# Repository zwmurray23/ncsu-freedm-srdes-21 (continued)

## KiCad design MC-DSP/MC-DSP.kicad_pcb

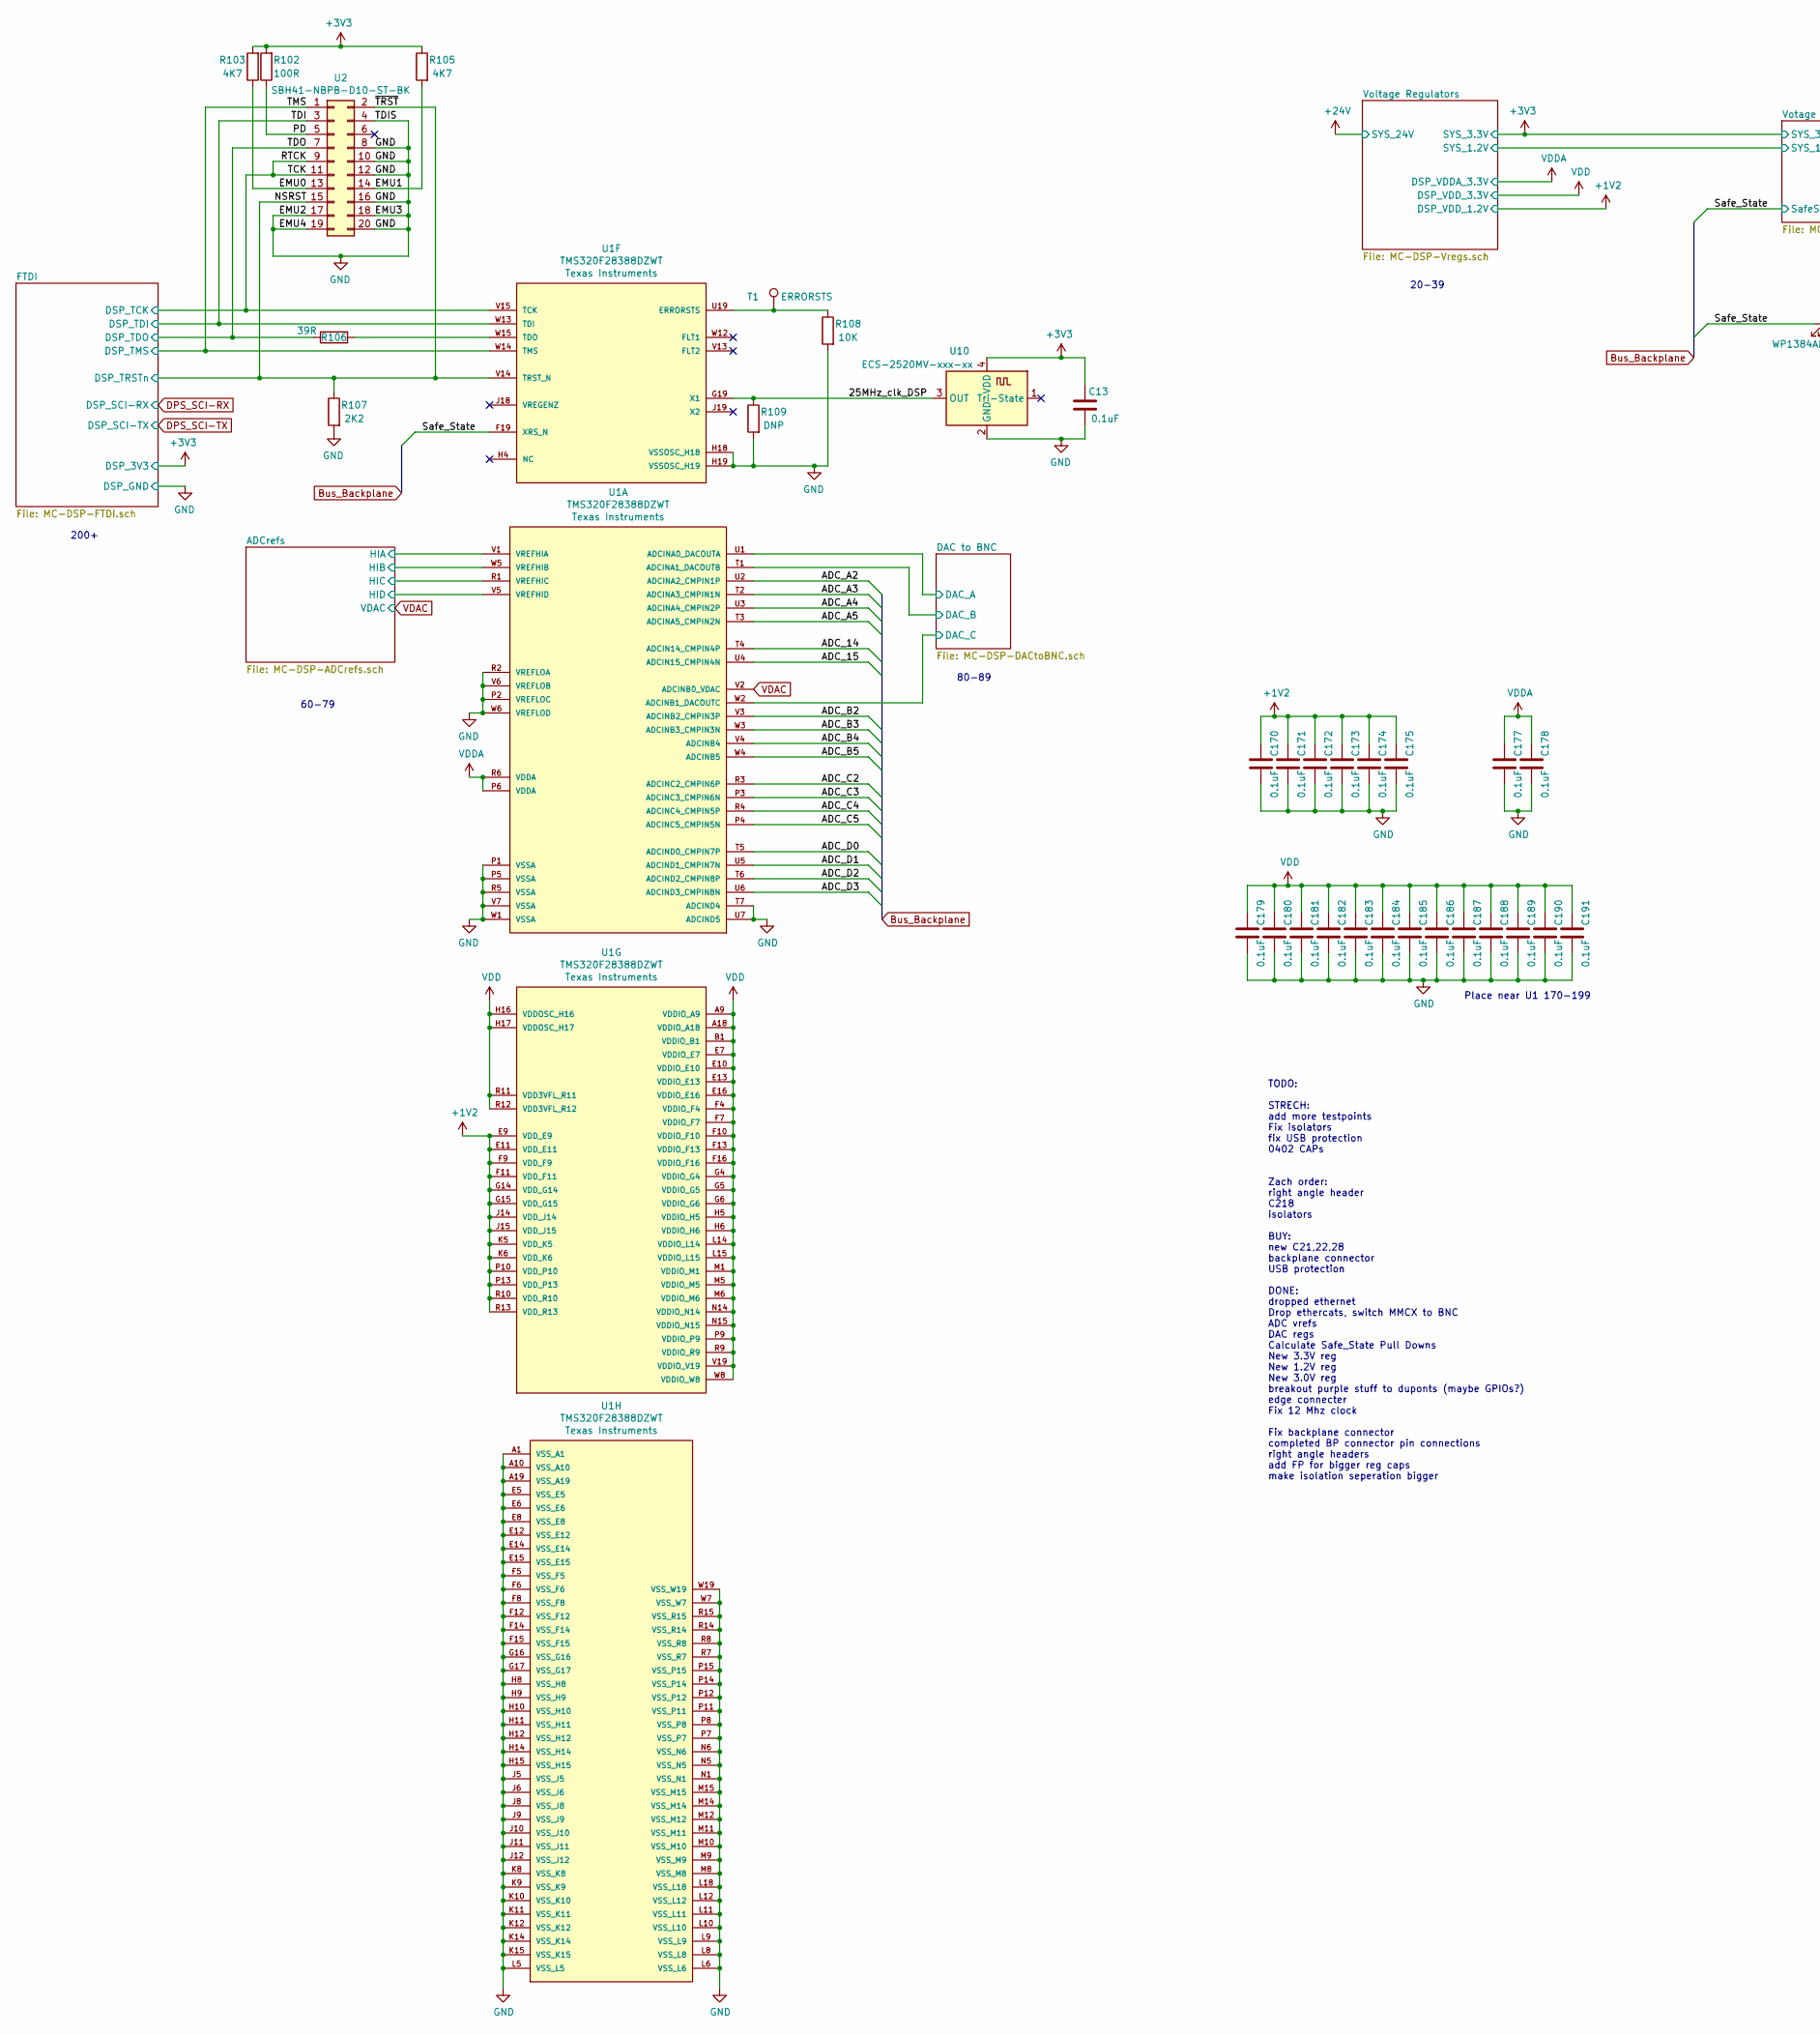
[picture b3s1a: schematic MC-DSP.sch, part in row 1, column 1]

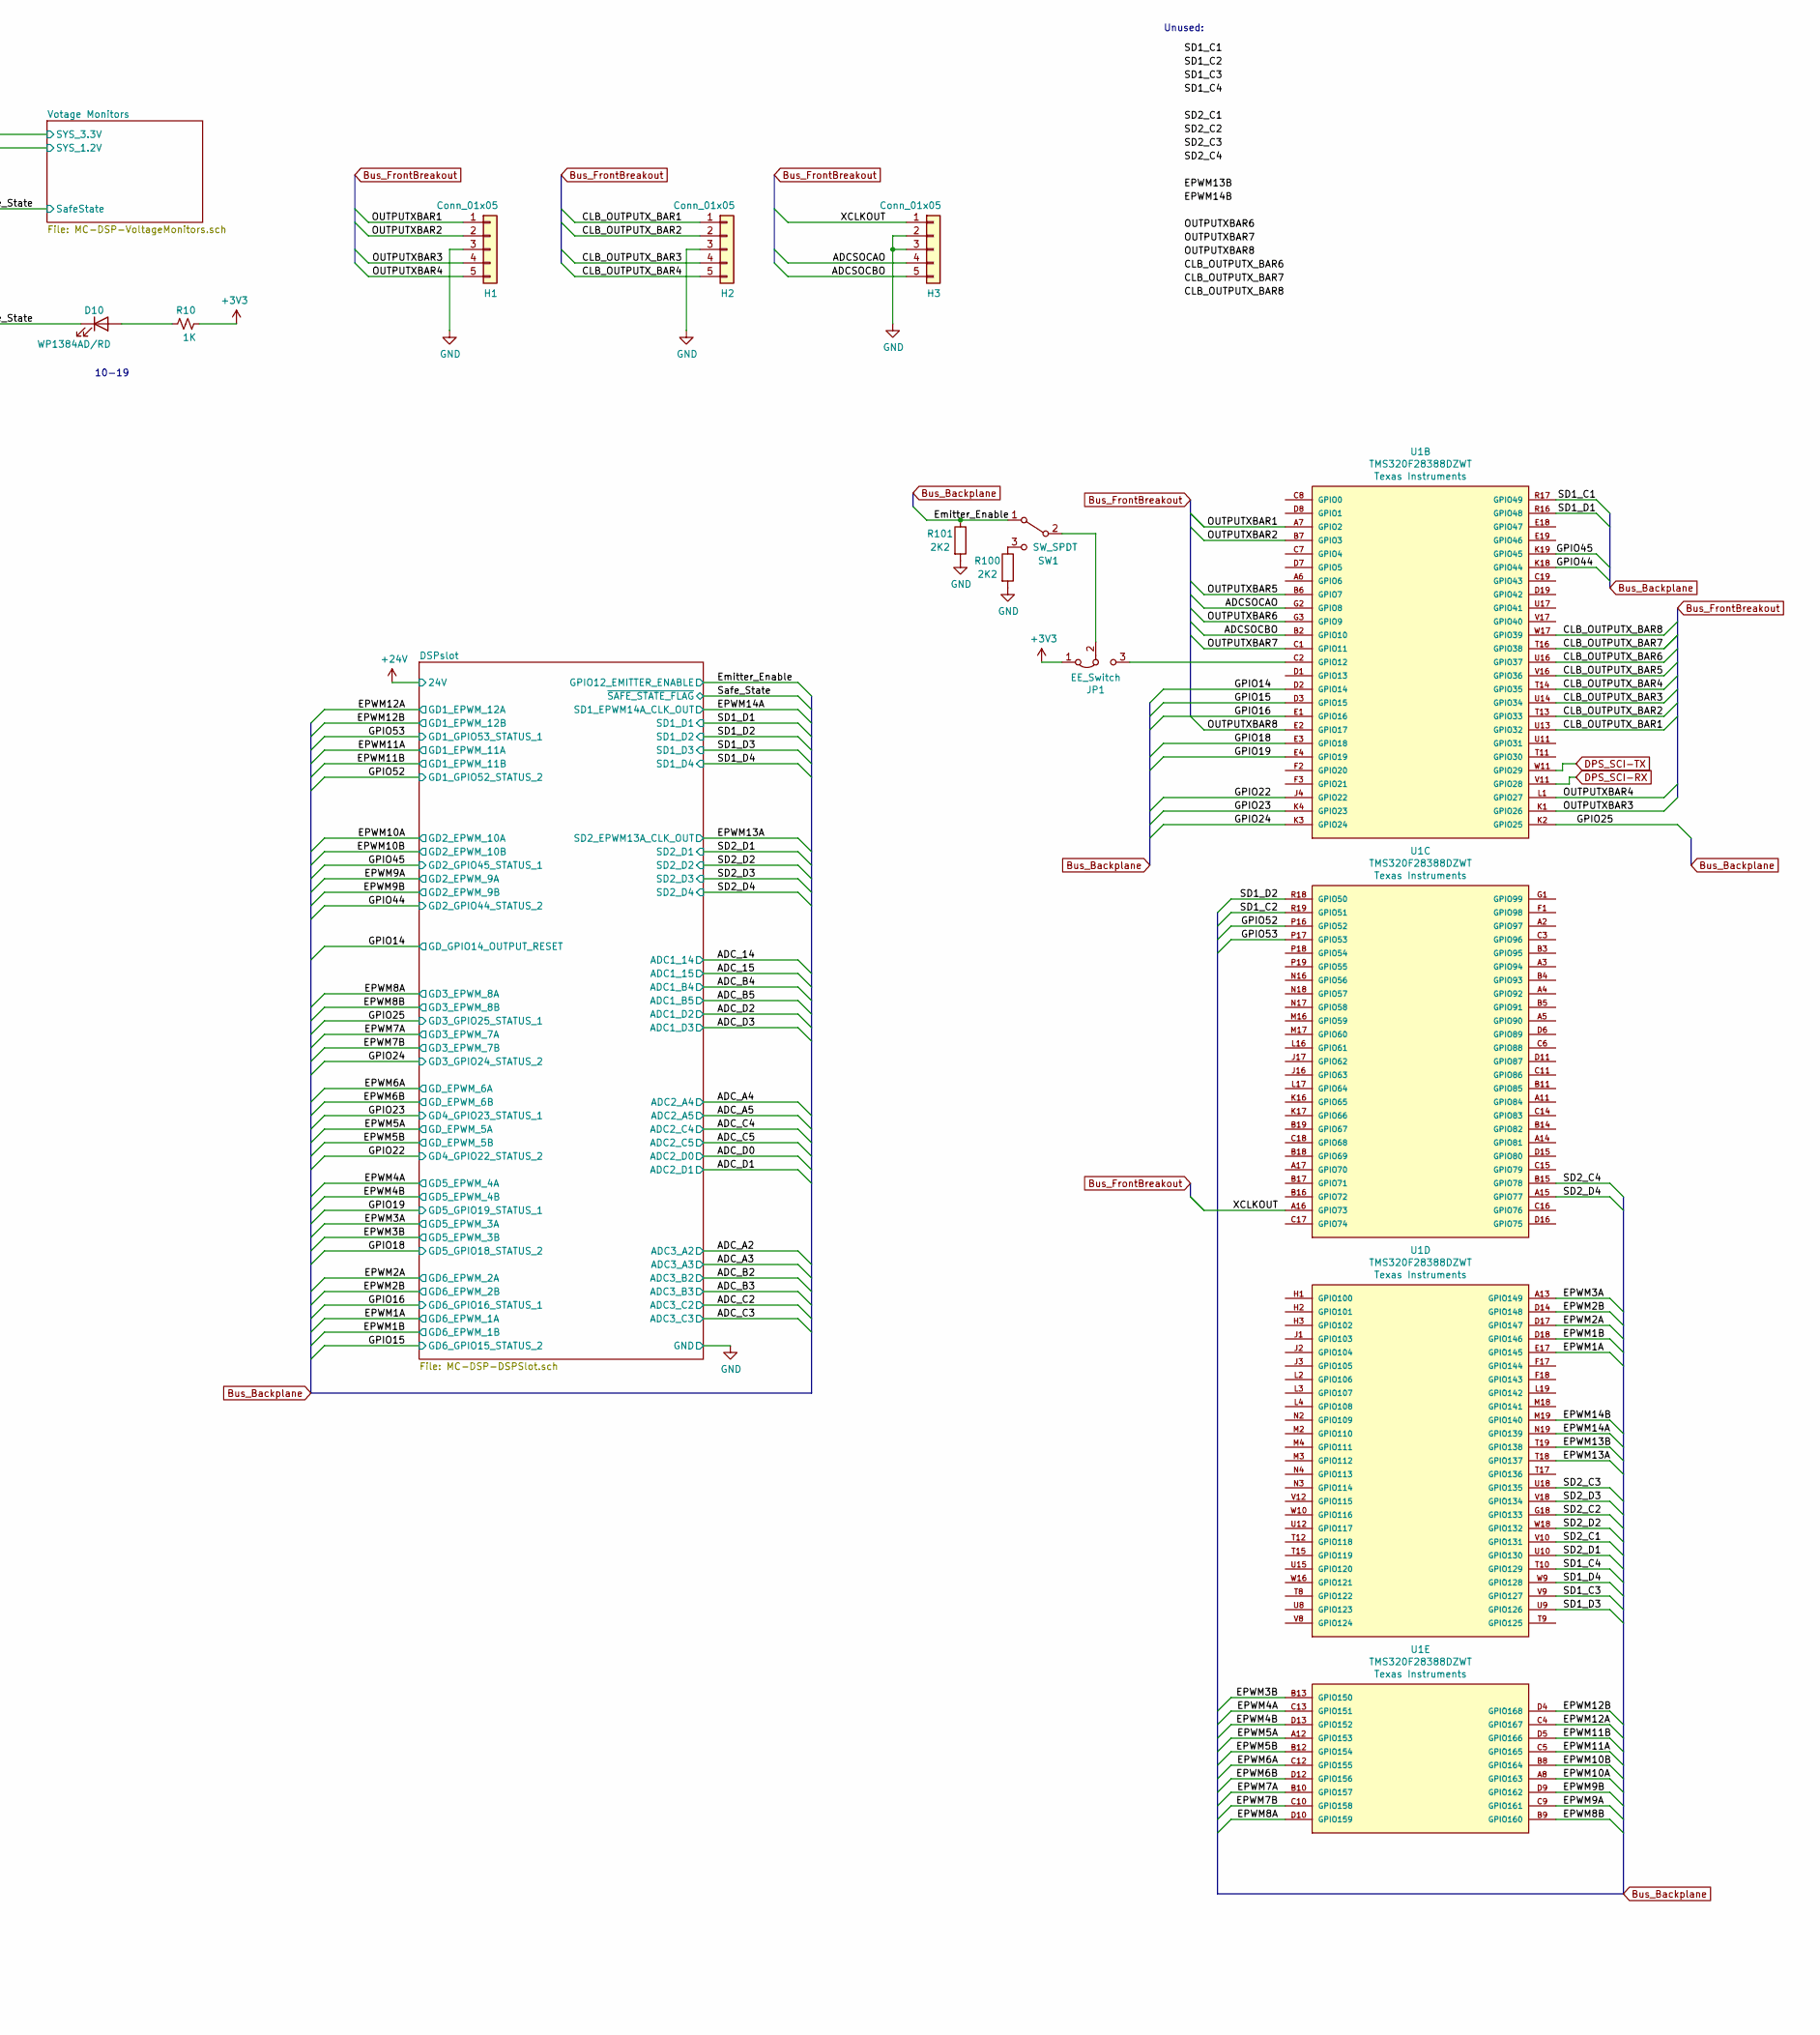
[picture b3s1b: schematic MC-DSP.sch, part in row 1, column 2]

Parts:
C13: 0.1uF; C_0603_1608Metric_Pad1.08x0.95mm_HandSolder
C170, C171, C172, C173, C174, C175, C177, C178, C179, C180, C181, C182, C183, C184, C185, C186, C187, C188, C189, C190, C191: 0.1uF; C_0402_1005Metric_Pad0.74x0.62mm_HandSolder
D10: WP1384AD/RD; LED_D3.0mm
H1, H2, H3: Conn_01x05; PinSocket_1x05_P2.54mm_Vertical
JP1: EE_Switch; PinSocket_1x03_P2.54mm_Vertical
R10: 1K; R_0603_1608Metric_Pad0.98x0.95mm_HandSolder
R100, R101, R107: 2K2; R_0603_1608Metric_Pad0.98x0.95mm_HandSolder
R102: 100R; R_0603_1608Metric_Pad0.98x0.95mm_HandSolder
R103, R105: 4K7; R_0603_1608Metric_Pad0.98x0.95mm_HandSolder
R106: 39R; R_0603_1608Metric_Pad0.98x0.95mm_HandSolder
R108: 10K; R_0603_1608Metric_Pad0.98x0.95mm_HandSolder
R109: DNP; R_0603_1608Metric_Pad0.98x0.95mm_HandSolder
SW1: SW_SPDT; GT12MABE
T1: ERRORSTS; TestPoint_Pad_D1.5mm
U1: TMS320F28388DZWT; BGA337C80P19X19_1600X1600X140N
U2: SBH41-NBPB-D10-ST-BK
U10: ECS-2520MV-xxx-xx; Oscillator_SMD_ECS_2520MV-xxx-xx-4Pin_2.5x2.0mm

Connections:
+1V2: C170.2, C171.2, C172.2, C173.2, C174.2, C175.2, U1.E9 (VDD_E9), U1.E11 (VDD_E11), U1.F9 (VDD_F9), U1.F11 (VDD_F11), U1.G14 (VDD_G14), U1.G15 (VDD_G15), U1.J14 (VDD_J14), U1.J15 (VDD_J15), U1.K5 (VDD_K5), U1.K6 (VDD_K6), U1.P10 (VDD_P10), U1.P13 (VDD_P13), U1.R10 (VDD_R10), U1.R13 (VDD_R13); also elsewhere on the board
+3V3: C13.2, JP1.1 (A), R10.1, R102.2, R103.2, R105.1, U10.4 (VDD); also elsewhere on the board
/25MHz_clk_DSP: R109.1, U1.G19 (X1), U10.3 (OUT)
/ADCSOCAO: H3.4, U1.G2 (GPIO8)
/ADCSOCBO: H3.5, U1.B2 (GPIO10)
/ADC_14: U1.T4 (ADCIN14_CMPIN4P); also elsewhere on the board
/ADC_15: U1.U4 (ADCIN15_CMPIN4N); also elsewhere on the board
/ADC_A2: U1.U2 (ADCINA2_CMPIN1P); also elsewhere on the board
/ADC_A3: U1.T2 (ADCINA3_CMPIN1N); also elsewhere on the board
/ADC_A4: U1.U3 (ADCINA4_CMPIN2P); also elsewhere on the board
/ADC_A5: U1.T3 (ADCINA5_CMPIN2N); also elsewhere on the board
/ADC_B2: U1.V3 (ADCINB2_CMPIN3P); also elsewhere on the board
/ADC_B3: U1.W3 (ADCINB3_CMPIN3N); also elsewhere on the board
/ADC_B4: U1.V4 (ADCINB4); also elsewhere on the board
/ADC_B5: U1.W4 (ADCINB5); also elsewhere on the board
/ADC_C2: U1.R3 (ADCINC2_CMPIN6P); also elsewhere on the board
/ADC_C3: U1.P3 (ADCINC3_CMPIN6N); also elsewhere on the board
/ADC_C4: U1.R4 (ADCINC4_CMPIN5P); also elsewhere on the board
/ADC_C5: U1.P4 (ADCINC5_CMPIN5N); also elsewhere on the board
/ADC_D0: U1.T5 (ADCIND0_CMPIN7P); also elsewhere on the board
/ADC_D1: U1.U5 (ADCIND1_CMPIN7N); also elsewhere on the board
/ADC_D2: U1.T6 (ADCIND2_CMPIN8P); also elsewhere on the board
/ADC_D3: U1.U6 (ADCIND3_CMPIN8N); also elsewhere on the board
/ADCrefs/HIA: U1.V1 (VREFHIA); also elsewhere on the board
/ADCrefs/HIB: U1.W5 (VREFHIB); also elsewhere on the board
/ADCrefs/HIC: U1.R1 (VREFHIC); also elsewhere on the board
/ADCrefs/HID: U1.V5 (VREFHID); also elsewhere on the board
/CLB_OUTPUTX_BAR1: H2.1, U1.U13 (GPIO32)
/CLB_OUTPUTX_BAR2: H2.2, U1.T13 (GPIO33)
/CLB_OUTPUTX_BAR3: H2.4, U1.U14 (GPIO34)
/CLB_OUTPUTX_BAR4: H2.5, U1.T14 (GPIO35)
/CLB_OUTPUTX_BAR5: U1.V16 (GPIO36)
/CLB_OUTPUTX_BAR6: U1.U16 (GPIO37)
/CLB_OUTPUTX_BAR7: U1.T16 (GPIO38)
/CLB_OUTPUTX_BAR8: U1.W17 (GPIO39)
/DAC to BNC/DAC_A: U1.U1 (ADCINA0_DACOUTA); also elsewhere on the board
/DAC to BNC/DAC_B: U1.T1 (ADCINA1_DACOUTB); also elsewhere on the board
/DAC to BNC/DAC_C: U1.W2 (ADCINB1_DACOUTC); also elsewhere on the board
/EMU0: R103.1, U2.13
/EMU1: R105.2, U2.14
/EPWM1A: U1.E17 (GPIO145); also elsewhere on the board
/EPWM1B: U1.D18 (GPIO146); also elsewhere on the board
/EPWM2A: U1.D17 (GPIO147); also elsewhere on the board
/EPWM2B: U1.D14 (GPIO148); also elsewhere on the board
/EPWM3A: U1.A13 (GPIO149); also elsewhere on the board
/EPWM3B: U1.B13 (GPIO150); also elsewhere on the board
/EPWM4A: U1.C13 (GPIO151); also elsewhere on the board
/EPWM4B: U1.D13 (GPIO152); also elsewhere on the board
/EPWM5A: U1.A12 (GPIO153); also elsewhere on the board
/EPWM5B: U1.B12 (GPIO154); also elsewhere on the board
/EPWM6A: U1.C12 (GPIO155); also elsewhere on the board
/EPWM6B: U1.D12 (GPIO156); also elsewhere on the board
/EPWM7A: U1.B10 (GPIO157); also elsewhere on the board
/EPWM7B: U1.C10 (GPIO158); also elsewhere on the board
/EPWM8A: U1.D10 (GPIO159); also elsewhere on the board
/EPWM8B: U1.B9 (GPIO160); also elsewhere on the board
/EPWM9A: U1.C9 (GPIO161); also elsewhere on the board
/EPWM9B: U1.D9 (GPIO162); also elsewhere on the board
/EPWM10A: U1.A8 (GPIO163); also elsewhere on the board
/EPWM10B: U1.B8 (GPIO164); also elsewhere on the board
/EPWM11A: U1.C5 (GPIO165); also elsewhere on the board
/EPWM11B: U1.D5 (GPIO166); also elsewhere on the board
/EPWM12A: U1.C4 (GPIO167); also elsewhere on the board
/EPWM12B: U1.D4 (GPIO168); also elsewhere on the board
/EPWM13A: U1.T18 (GPIO137); also elsewhere on the board
/EPWM13B: U1.T19 (GPIO138)
/EPWM14A: U1.N19 (GPIO139); also elsewhere on the board
/EPWM14B: U1.M19 (GPIO140)
/Emitter_Enable: R101.1, SW1.1 (A); also elsewhere on the board
/GPIO14: U1.D2 (GPIO14); also elsewhere on the board
/GPIO15: U1.D3 (GPIO15); also elsewhere on the board
/GPIO16: U1.E1 (GPIO16); also elsewhere on the board
/GPIO18: U1.E3 (GPIO18); also elsewhere on the board
/GPIO19: U1.E4 (GPIO19); also elsewhere on the board
/GPIO22: U1.J4 (GPIO22); also elsewhere on the board
/GPIO23: U1.K4 (GPIO23); also elsewhere on the board
/GPIO24: U1.K3 (GPIO24); also elsewhere on the board
/GPIO25: U1.K2 (GPIO25); also elsewhere on the board
/GPIO44: U1.K18 (GPIO44); also elsewhere on the board
/GPIO45: U1.K19 (GPIO45); also elsewhere on the board
/GPIO52: U1.P16 (GPIO52); also elsewhere on the board
/GPIO53: U1.P17 (GPIO53); also elsewhere on the board
/NSRST: R107.1, U1.V14 (TRST_N), U2.2, U2.15; also elsewhere on the board
/OUTPUTXBAR1: H1.1, U1.A7 (GPIO2)
/OUTPUTXBAR2: H1.2, U1.B7 (GPIO3)
/OUTPUTXBAR3: H1.4, U1.K1 (GPIO26)
/OUTPUTXBAR4: H1.5, U1.L1 (GPIO27)
/OUTPUTXBAR5: U1.B6 (GPIO7)
/OUTPUTXBAR6: U1.G3 (GPIO9)
/OUTPUTXBAR7: U1.C1 (GPIO11)
/OUTPUTXBAR8: U1.E2 (GPIO17)
/PD: R102.1, U2.5
/RTCK: U1.V15 (TCK), U2.9, U2.11; also elsewhere on the board
/SD1_C1: U1.R17 (GPIO49)
/SD1_C2: U1.R19 (GPIO51)
/SD1_C3: U1.V9 (GPIO127)
/SD1_C4: U1.T10 (GPIO129)
/SD1_D1: U1.R16 (GPIO48); also elsewhere on the board
/SD1_D2: U1.R18 (GPIO50); also elsewhere on the board
/SD1_D3: U1.U9 (GPIO126); also elsewhere on the board
/SD1_D4: U1.W9 (GPIO128); also elsewhere on the board
/SD2_C1: U1.V10 (GPIO131)
/SD2_C2: U1.G18 (GPIO133)
/SD2_C3: U1.U18 (GPIO135)
/SD2_C4: U1.B15 (GPIO78)
/SD2_D1: U1.U10 (GPIO130); also elsewhere on the board
/SD2_D2: U1.W18 (GPIO132); also elsewhere on the board
/SD2_D3: U1.V18 (GPIO134); also elsewhere on the board
/SD2_D4: U1.A15 (GPIO77); also elsewhere on the board
/Safe_State: D10.1 (K), U1.F19 (XRS_N); also elsewhere on the board
/TDI: U1.W13 (TDI), U2.3; also elsewhere on the board
/TDO: R106.1, U2.7; also elsewhere on the board
/TMS: U1.W14 (TMS), U2.1; also elsewhere on the board
/XCLKOUT: H3.1, U1.A16 (GPIO73)
DPS_SCI-RX: U1.V11 (GPIO28); also elsewhere on the board
DPS_SCI-TX: U1.W11 (GPIO29); also elsewhere on the board
GND: C13.1, C170.1, C171.1, C172.1, C173.1, C174.1, C175.1, C177.1, C178.1, C179.1, C180.1, C181.1, C182.1, C183.1, C184.1, C185.1, C186.1, C187.1, C188.1, C189.1, C190.1, C191.1, H1.3, H2.3, H3.2, H3.3, R100.2, R101.2, R107.2, R108.2, R109.2, U1.A1 (VSS_A1), U1.A10 (VSS_A10), U1.A19 (VSS_A19), U1.E5 (VSS_E5), U1.E6 (VSS_E6), U1.E8 (VSS_E8), U1.E12 (VSS_E12), U1.E14 (VSS_E14), U1.E15 (VSS_E15), U1.F5 (VSS_F5), U1.F6 (VSS_F6), U1.F8 (VSS_F8), U1.F12 (VSS_F12), U1.F14 (VSS_F14), U1.F15 (VSS_F15), U1.G16 (VSS_G16), U1.G17 (VSS_G17), U1.H8 (VSS_H8), U1.H9 (VSS_H9), U1.H10 (VSS_H10), U1.H11 (VSS_H11), U1.H12 (VSS_H12), U1.H14 (VSS_H14), U1.H15 (VSS_H15), U1.H18 (VSSOSC_H18), U1.H19 (VSSOSC_H19), U1.J5 (VSS_J5), U1.J6 (VSS_J6), U1.J8 (VSS_J8), U1.J9 (VSS_J9), U1.J10 (VSS_J10), U1.J11 (VSS_J11), U1.J12 (VSS_J12), U1.K8 (VSS_K8), U1.K9 (VSS_K9), U1.K10 (VSS_K10), U1.K11 (VSS_K11), U1.K12 (VSS_K12), U1.K14 (VSS_K14), U1.K15 (VSS_K15), U1.L5 (VSS_L5), U1.L6 (VSS_L6), U1.L8 (VSS_L8), U1.L9 (VSS_L9), U1.L10 (VSS_L10), U1.L11 (VSS_L11), U1.L12 (VSS_L12), U1.L18 (VSS_L18), U1.M8 (VSS_M8), U1.M9 (VSS_M9), U1.M10 (VSS_M10), U1.M11 (VSS_M11), U1.M12 (VSS_M12), U1.M14 (VSS_M14), U1.M15 (VSS_M15), U1.N1 (VSS_N1), U1.N5 (VSS_N5), U1.N6 (VSS_N6), U1.P1 (VSSA), U1.P2 (VREFLOC), U1.P5 (VSSA), U1.P7 (VSS_P7), U1.P8 (VSS_P8), U1.P11 (VSS_P11), U1.P12 (VSS_P12), U1.P14 (VSS_P14), U1.P15 (VSS_P15), U1.R2 (VREFLOA), U1.R5 (VSSA), U1.R7 (VSS_R7), U1.R8 (VSS_R8), U1.R14 (VSS_R14), U1.R15 (VSS_R15), U1.T7 (ADCIND4), U1.U7 (ADCIND5), U1.V6 (VREFLOB), U1.V7 (VSSA), U1.W1 (VSSA), U1.W6 (VREFLOD), U1.W7 (VSS_W7), U1.W19 (VSS_W19), U2.4, U2.8, U2.10, U2.12, U2.16, U2.17, U2.18, U2.19, U2.20, U10.2 (GND); also elsewhere on the board
unnamed: D10.2 (A), R10.2
unnamed: JP1.2 (C), SW1.2 (B)
unnamed: JP1.3 (B), U1.C2 (GPIO12)
unnamed: R100.1, SW1.3 (C)
unnamed: R106.2, U1.W15 (TDO)
unnamed: R108.1, T1.1, U1.U19 (ERRORSTS)
VDAC: U1.V2 (ADCINB0_VDAC); also elsewhere on the board
VDD: C179.2, C180.2, C181.2, C182.2, C183.2, C184.2, C185.2, C186.2, C187.2, C188.2, C189.2, C190.2, C191.2, U1.A9 (VDDIO_A9), U1.A18 (VDDIO_A18), U1.B1 (VDDIO_B1), U1.E7 (VDDIO_E7), U1.E10 (VDDIO_E10), U1.E13 (VDDIO_E13), U1.E16 (VDDIO_E16), U1.F4 (VDDIO_F4), U1.F7 (VDDIO_F7), U1.F10 (VDDIO_F10), U1.F13 (VDDIO_F13), U1.F16 (VDDIO_F16), U1.G4 (VDDIO_G4), U1.G5 (VDDIO_G5), U1.G6 (VDDIO_G6), U1.H5 (VDDIO_H5), U1.H6 (VDDIO_H6), U1.H16 (VDDOSC_H16), U1.H17 (VDDOSC_H17), U1.L14 (VDDIO_L14), U1.L15 (VDDIO_L15), U1.M1 (VDDIO_M1), U1.M5 (VDDIO_M5), U1.M6 (VDDIO_M6), U1.N14 (VDDIO_N14), U1.N15 (VDDIO_N15), U1.P9 (VDDIO_P9), U1.R9 (VDDIO_R9), U1.R11 (VDD3VFL_R11), U1.R12 (VDD3VFL_R12), U1.V19 (VDDIO_V19), U1.W8 (VDDIO_W8); also elsewhere on the board
VDDA: C177.2, C178.2, U1.P6 (VDDA), U1.R6 (VDDA); also elsewhere on the board

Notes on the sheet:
60-79
80-89
200+
10-19
20-39
Place near U1 170-199
TODO: STRECH: add more testpoints Fix isolators fix USB protection 0402 CAPs Zach order: right angle header C218 isolators BUY: new C21,22,28 backplane connector USB protection DONE: dropped ethernet Drop ethercats, switch MMCX to BNC ADC vrefs DAC regs Calculate Safe_State Pull Downs New 3.3V reg 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
Unused:

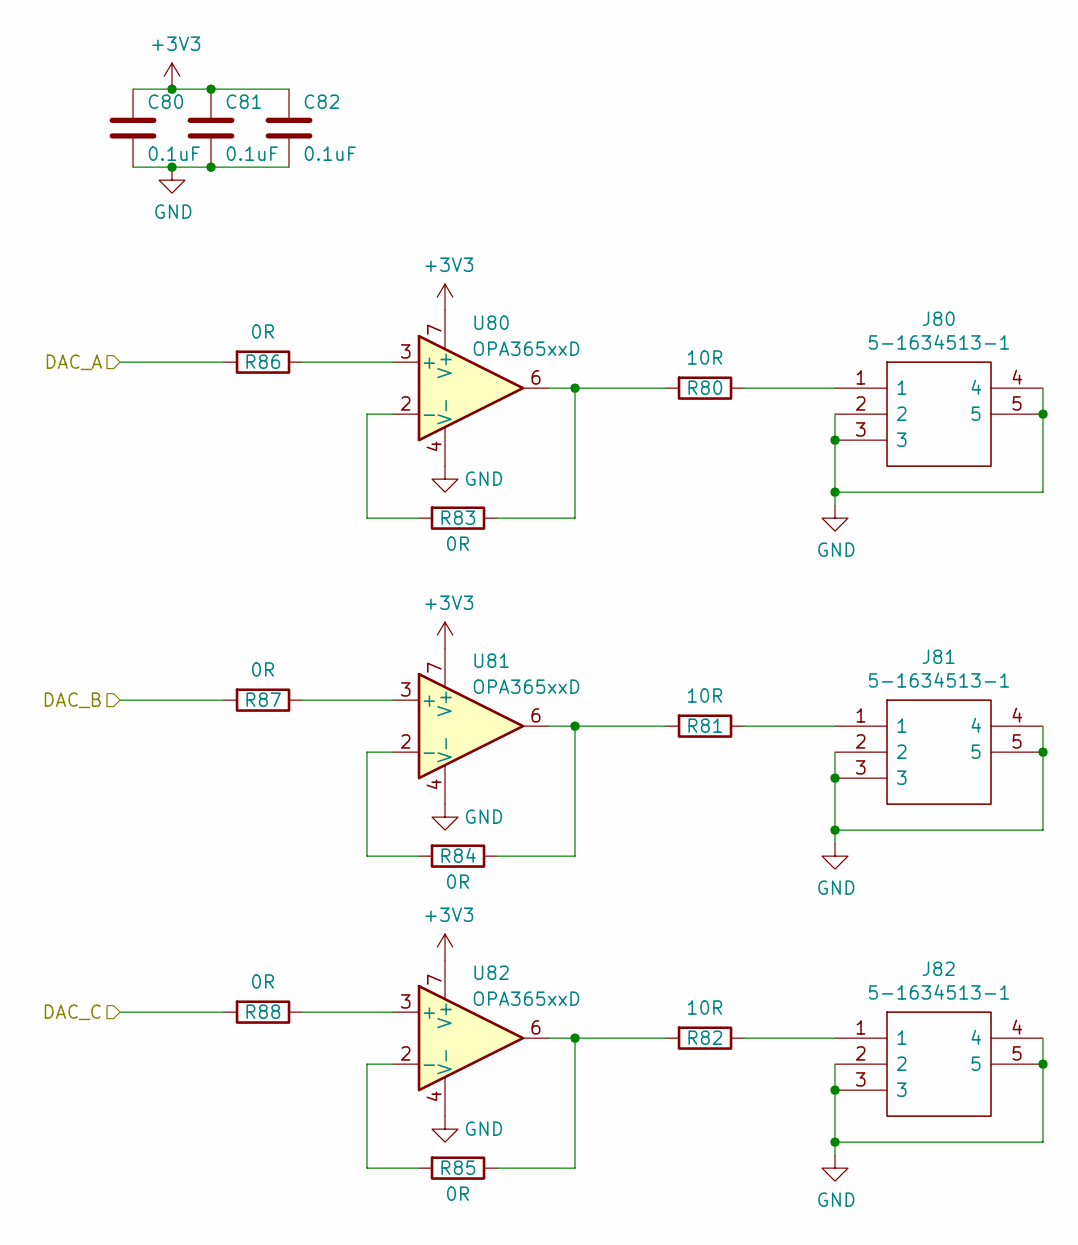
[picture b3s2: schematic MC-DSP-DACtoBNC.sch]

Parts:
C80, C81, C82: 0.1uF; C_0603_1608Metric_Pad1.08x0.95mm_HandSolder
J80, J81, J82: 5-1634513-1; 516345131; Manufacturer_Part_Number 5-1634513-1; Mouser Part Number 571-5-1634513-1
R80, R81, R82: 10R; R_0603_1608Metric_Pad0.98x0.95mm_HandSolder
R83, R84, R85, R86, R87, R88: 0R; R_0603_1608Metric_Pad0.98x0.95mm_HandSolder
U80, U81, U82: OPA365xxD; SOIC-8_3.9x4.9mm_P1.27mm

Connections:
+3V3: C80.2, C81.2, C82.2, U80.7 (V+), U81.7 (V+), U82.7 (V+); also elsewhere on the board
/DAC to BNC/DAC_A: R86.2; also elsewhere on the board
/DAC to BNC/DAC_B: R87.2; also elsewhere on the board
/DAC to BNC/DAC_C: R88.2; also elsewhere on the board
GND: C80.1, C81.1, C82.1, J80.2, J80.3, J80.4, J80.5, J81.2, J81.3, J81.4, J81.5, J82.2, J82.3, J82.4, J82.5, U80.4 (V-), U81.4 (V-), U82.4 (V-); also elsewhere on the board
unnamed: J80.1, R80.1
unnamed: J81.1, R81.1
unnamed: J82.1, R82.1
unnamed: R80.2, R83.1, U80.6
unnamed: R81.2, R84.1, U81.6
unnamed: R82.2, R85.1, U82.6
unnamed: R83.2, U80.2 (-)
unnamed: R84.2, U81.2 (-)
unnamed: R85.2, U82.2 (-)
unnamed: R86.1, U80.3 (+)
unnamed: R87.1, U81.3 (+)
unnamed: R88.1, U82.3 (+)

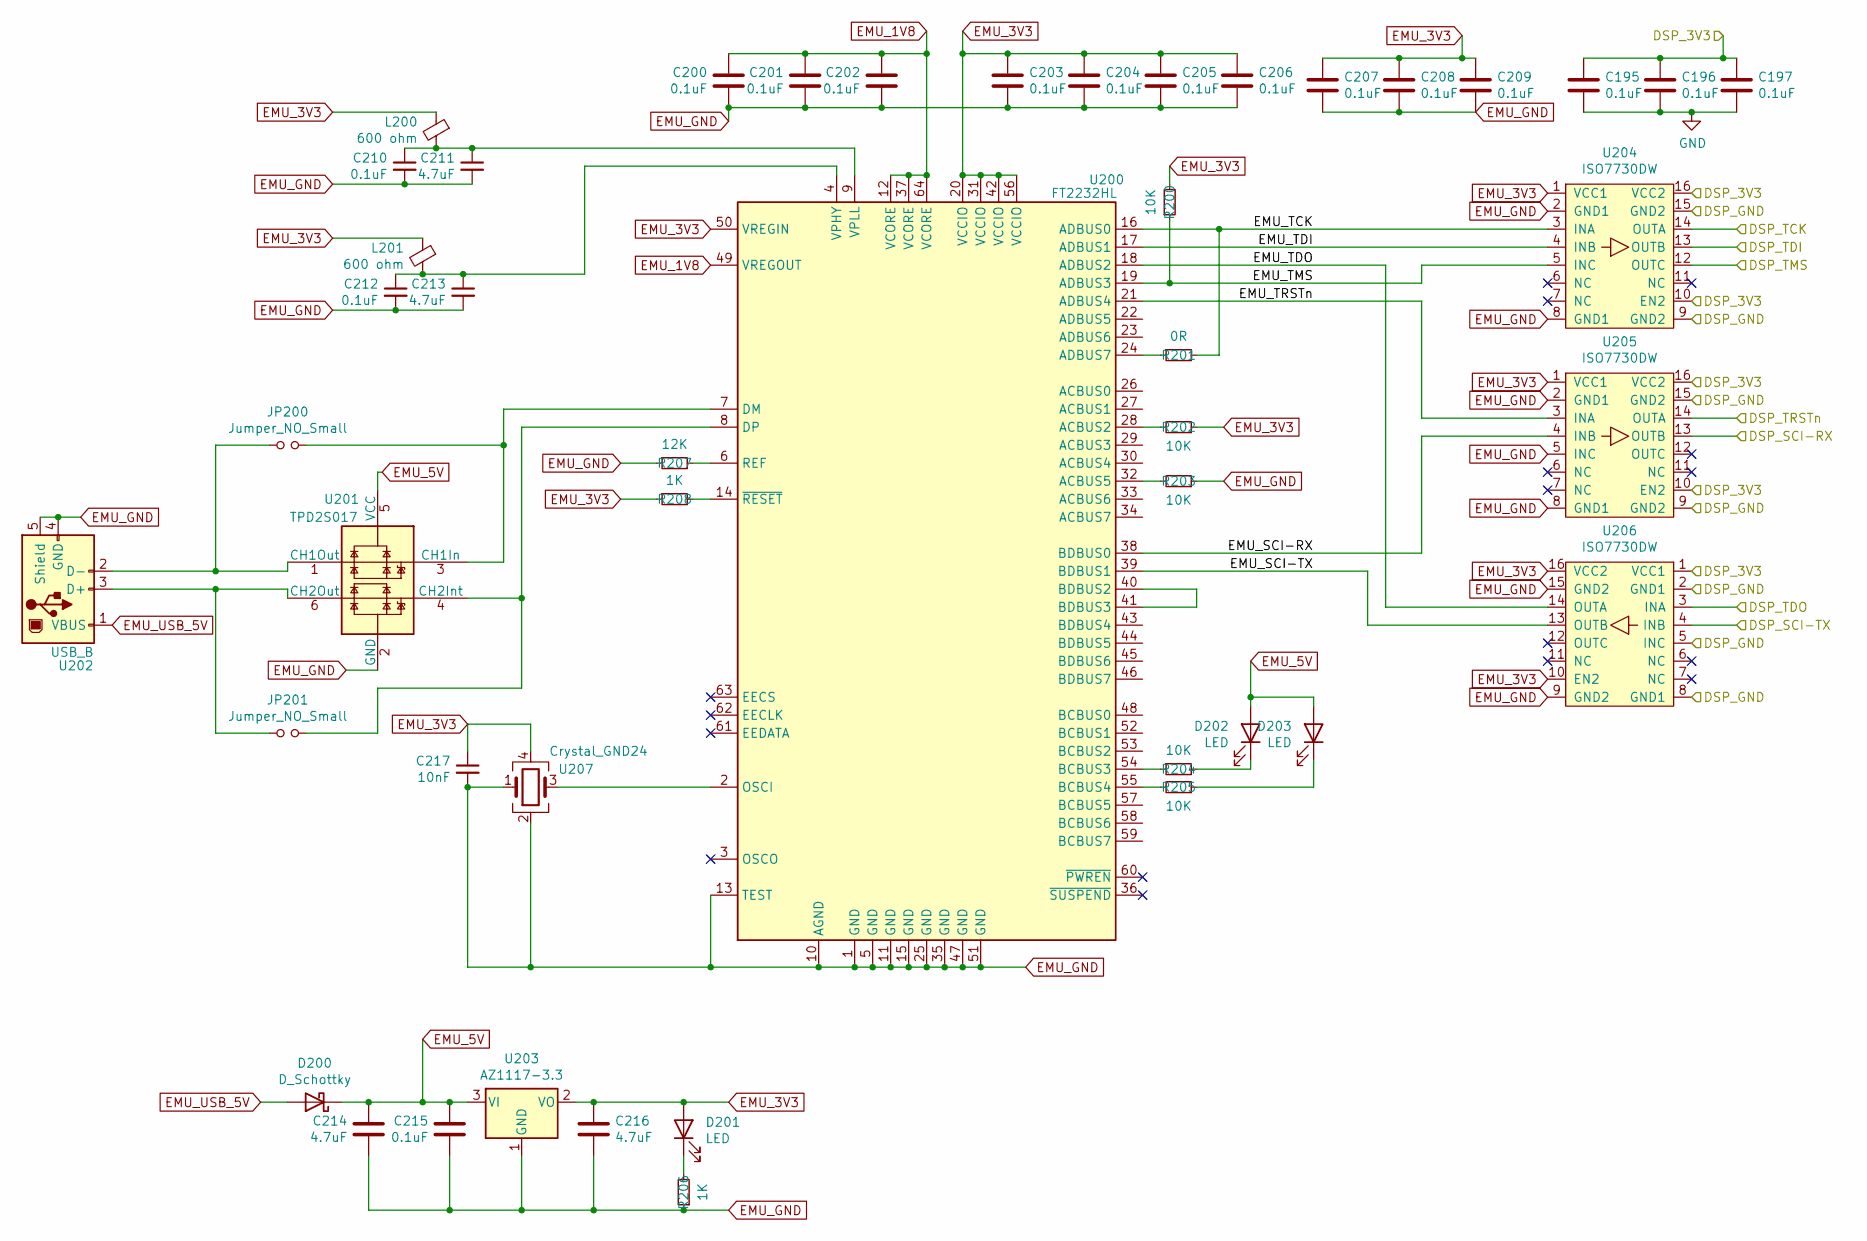
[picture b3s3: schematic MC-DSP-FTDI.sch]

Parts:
C195, C196, C197, C200, C201, C202, C203, C204, C205, C206, C207, C208, C209, C210, C212, C215: 0.1uF; C_0603_1608Metric_Pad1.08x0.95mm_HandSolder
C211, C213, C214, C216: 4.7uF; C_0603_1608Metric_Pad1.08x0.95mm_HandSolder
C217: 10nF; C_0603_1608Metric_Pad1.08x0.95mm_HandSolder
D200: D_Schottky; D_SMF
D201, D202, D203: LED; LED_D3.0mm
JP200, JP201: Jumper_NO_Small; SolderJumper-2_P1.3mm_Open_RoundedPad1.0x1.5mm
L200, L201: 600 ohm; L_0805_2012Metric_Pad1.05x1.20mm_HandSolder
R200, R202, R203, R204, R205: 10K; R_0603_1608Metric_Pad0.98x0.95mm_HandSolder
R201: 0R; R_0603_1608Metric_Pad0.98x0.95mm_HandSolder
R206, R208: 1K; R_0603_1608Metric_Pad0.98x0.95mm_HandSolder
R207: 12K; R_0603_1608Metric_Pad0.98x0.95mm_HandSolder
U200: FT2232HL; LQFP-64_10x10mm_P0.5mm
U201: TPD2S017; SOT-23-6
U202: USB_B; USB_B_OST_USB-B1HSxx_Horizontal
U203: AZ1117-3.3; SOT-89-3_Handsoldering
U204, U205, U206: ISO7730DW; SOIC-16W_7.5x10.3mm_P1.27mm
U207: Crystal_GND24; Oscillator_SMD_TXC_7C-4Pin_5.0x3.2mm_HandSoldering

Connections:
+3V3: C195.1, C196.1, C197.1, U204.10 (EN2), U204.16 (VCC2), U205.10 (EN2), U205.16 (VCC2), U206.1 (VCC1); also elsewhere on the board
/FTDI/EMU_SCI-RX: U200.38 (BDBUS0), U205.4 (INB)
/FTDI/EMU_SCI-TX: U200.39 (BDBUS1), U206.13 (OUTB)
/FTDI/EMU_TCK: R201.2, U200.16 (ADBUS0), U204.3 (INA)
/FTDI/EMU_TDI: U200.17 (ADBUS1), U204.4 (INB)
/FTDI/EMU_TDO: U200.18 (ADBUS2), U206.14 (OUTA)
/FTDI/EMU_TMS: R200.1, U200.19 (ADBUS3), U204.5 (INC)
/FTDI/EMU_TRSTn: U200.21 (ADBUS4), U205.3 (INA)
/NSRST: U205.14 (OUTA); also elsewhere on the board
/RTCK: U204.14 (OUTA); also elsewhere on the board
/TDI: U204.13 (OUTB); also elsewhere on the board
/TDO: U206.3 (INA); also elsewhere on the board
/TMS: U204.12 (OUTC); also elsewhere on the board
DPS_SCI-RX: U205.13 (OUTB); also elsewhere on the board
DPS_SCI-TX: U206.4 (INB); also elsewhere on the board
EMU_1V8: C200.1, C201.1, C202.1, U200.12 (VCORE), U200.37 (VCORE), U200.49 (VREGOUT), U200.64 (VCORE)
EMU_3V3: C203.1, C204.1, C205.1, C206.1, C207.1, C208.1, C209.1, C216.1, C217.1, D201.2 (A), L200.1, L201.1, R200.2, R202.1, R208.1, U200.20 (VCCIO), U200.31 (VCCIO), U200.42 (VCCIO), U200.50 (VREGIN), U200.56 (VCCIO), U203.2 (VO), U204.1 (VCC1), U205.1 (VCC1), U206.10 (EN2), U206.16 (VCC2), U207.4
EMU_5V: C214.1, C215.1, D200.1 (K), D202.2 (A), D203.2 (A), U201.5 (VCC), U203.3 (VI)
EMU_GND: C200.2, C201.2, C202.2, C203.2, C204.2, C205.2, C206.2, C207.2, C208.2, C209.2, C210.2, C211.2, C212.2, C213.2, C214.2, C215.2, C216.2, C217.2, R203.1, R206.1, R207.1, U200.1 (GND), U200.5 (GND), U200.10 (AGND), U200.11 (GND), U200.13 (TEST), U200.15 (GND), U200.25 (GND), U200.35 (GND), U200.47 (GND), U200.51 (GND), U201.2 (GND), U202.4 (GND), U202.5 (Shield), U203.1 (GND), U204.2 (GND1), U204.8 (GND1), U205.2 (GND1), U205.5 (INC), U205.8 (GND1), U206.9 (GND2), U206.15 (GND2), U207.1, U207.2; also elsewhere on the board
EMU_USB_5V: D200.2 (A), U202.1 (VBUS)
GND: C195.2, C196.2, C197.2, U204.9 (GND2), U204.15 (GND2), U205.9 (GND2), U205.15 (GND2), U206.2 (GND1), U206.5 (INC), U206.8 (GND1); also elsewhere on the board
unnamed: C210.1, C211.1, L200.2, U200.9 (VPLL)
unnamed: C212.1, C213.1, L201.2, U200.4 (VPHY)
unnamed: D201.1 (K), R206.2
unnamed: D202.1 (K), R204.2
unnamed: D203.1 (K), R205.1
unnamed: JP200.1, U201.1 (CH1Out), U202.2 (D-)
unnamed: JP200.2, U200.7 (DM), U201.3 (CH1In)
unnamed: JP201.1, U201.6 (CH2Out), U202.3 (D+)
unnamed: JP201.2, U200.8 (DP), U201.4 (CH2Int)
unnamed: R201.1, U200.24 (ADBUS7)
unnamed: R202.2, U200.28 (ACBUS2)
unnamed: R203.2, U200.32 (ACBUS5)
unnamed: R204.1, U200.54 (BCBUS3)
unnamed: R205.2, U200.55 (BCBUS4)
unnamed: R207.2, U200.6 (REF)
unnamed: R208.2, U200.14 (~RESET)
unnamed: U200.2 (OSCI), U207.3
unnamed: U200.40 (BDBUS2), U200.41 (BDBUS3)
